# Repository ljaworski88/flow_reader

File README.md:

# Streaming Potential Calculator

This is a pyqt5 application intended to be used with the sensor board included in the src/kicad folder and the Raspberry Pi.

The application is intended to determine the streaming potential of tissues placed within a chamber designed by my collegue by interfacing with two NAU7802 24-bit ADCs connected to seperate pressure transducers, the Sensirion SLG-150 flow meter, and the Keithley 6514 Electrometer.
The included install script should install the application and all required dependancies on a fresh Raspberry Pi install (changing the way sudo operates by default on the pi will break this functionality).

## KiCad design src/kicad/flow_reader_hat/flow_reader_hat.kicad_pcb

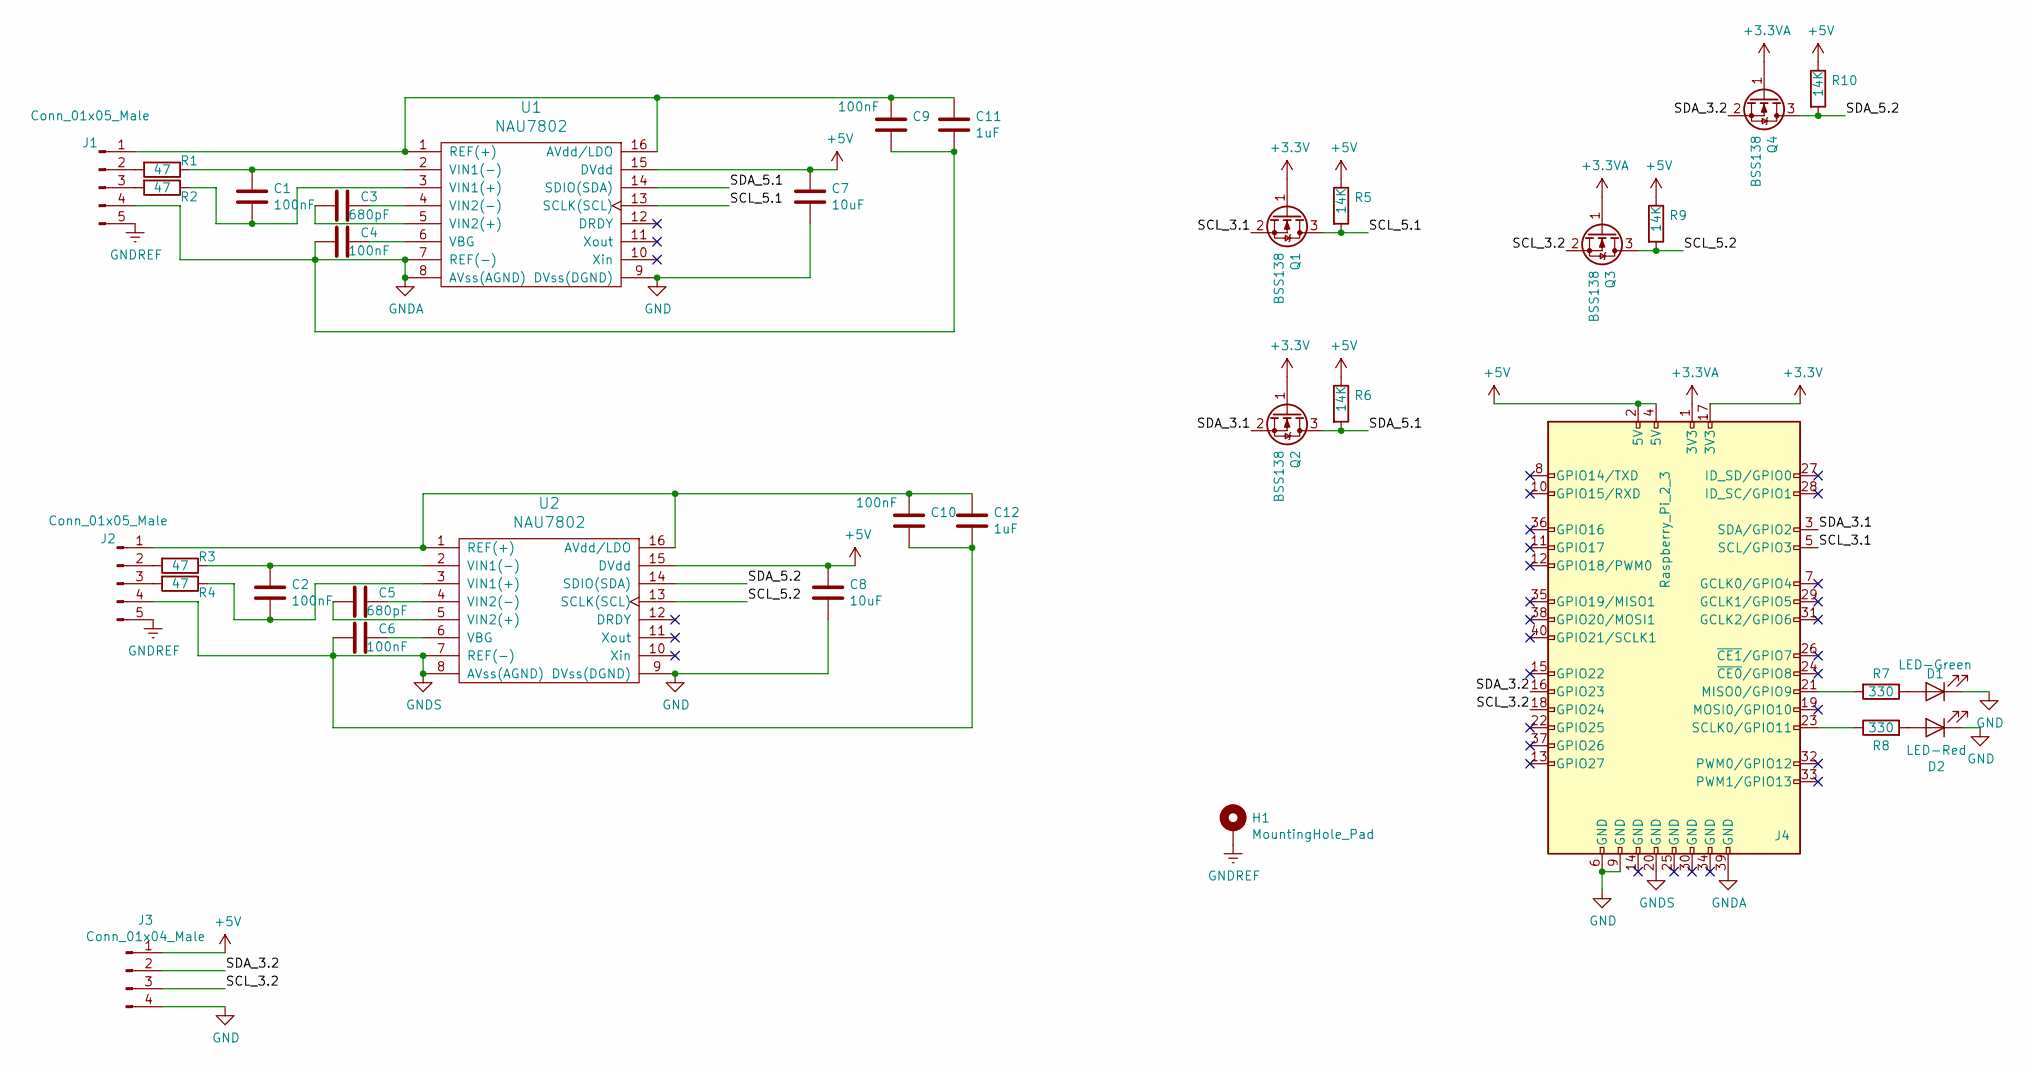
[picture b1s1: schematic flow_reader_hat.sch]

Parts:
C1, C2, C4, C6, C9, C10: 100nF; C_1206_3216Metric
C3, C5: 680pF; C_0805_2012Metric
C7, C8: 10uF; C_0805_2012Metric
C11, C12: 1uF; C_0805_2012Metric
D1: LED-Green; LED_0603_1608Metric_Castellated
D2: LED-Red; LED_0603_1608Metric_Castellated
H1: MountingHole_Pad; Banana_Jack_1Pin
J1, J2: Conn_01x05_Male; JST_EH_S5B-EH_1x05_P2.50mm_Horizontal
J3: Conn_01x04_Male; JST_EH_S4B-EH_1x04_P2.50mm_Horizontal
J4: Raspberry_Pi_2_3; Raspberry_Pi_Zero_Socketed_THT_FaceDown_MountingHoles
Q1, Q2, Q3, Q4: BSS138; SOT-23
R1, R2, R3, R4: 47; R_0805_2012Metric
R5, R6, R9, R10: 14K; R_0805_2012Metric
R7, R8: 330; R_0805_2012Metric
U1, U2: NAU7802; SOP-16_4.4x10.4mm_P1.27mm

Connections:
+3.3VA: J4.1 (3V3), Q3.1 (G), Q4.1 (G)
+3V3: J4.17 (3V3), Q1.1 (G), Q2.1 (G)
+5V: C7.1, C8.1, J3.1, J4.2 (5V), J4.4 (5V), R5.1, R6.1, R9.1, R10.1, U1.15 (DVdd), U2.15 (DVdd)
/SCL_3.1: J4.5 (SCL/GPIO3), Q1.2 (S)
/SCL_3.2: J3.3, J4.18 (GPIO24), Q3.2 (S)
/SCL_5.1: Q1.3 (D), R5.2, U1.13 (SCLK(SCL))
/SCL_5.2: Q3.3 (D), R9.2, U2.13 (SCLK(SCL))
/SDA_3.1: J4.3 (SDA/GPIO2), Q2.2 (S)
/SDA_3.2: J3.2, J4.16 (GPIO23), Q4.2 (S)
/SDA_5.1: Q2.3 (D), R6.2, U1.14 (SDIO(SDA))
/SDA_5.2: Q4.3 (D), R10.2, U2.14 (SDIO(SDA))
GND: C7.2, C8.2, D1.1 (K), D2.1 (K), J3.4, J4.6 (GND), J4.9 (GND), U1.9 (DVss(DGND)), U2.9 (DVss(DGND))
GNDA: C4.2, C9.2, C11.2, J1.4, J4.39 (GND), U1.7 (REF(-)), U1.8 (AVss(AGND))
GNDREF: H1.1, J1.5, J2.5
GNDS: C6.2, C10.2, C12.2, J2.4, J4.20 (GND), U2.7 (REF(-)), U2.8 (AVss(AGND))
unnamed: C1.1, R2.1, U1.3 (VIN1(+))
unnamed: C1.2, R1.1, U1.2 (VIN1(-))
unnamed: C2.1, R4.1, U2.3 (VIN1(+))
unnamed: C2.2, R3.1, U2.2 (VIN1(-))
unnamed: C3.1, U1.4 (VIN2(-))
unnamed: C3.2, U1.5 (VIN2(+))
unnamed: C4.1, U1.6 (VBG)
unnamed: C5.1, U2.4 (VIN2(-))
unnamed: C5.2, U2.5 (VIN2(+))
unnamed: C6.1, U2.6 (VBG)
unnamed: C10.1, C12.1, J2.1, U2.1 (REF(+)), U2.16 (AVdd/LDO)
unnamed: C9.1, C11.1, J1.1, U1.1 (REF(+)), U1.16 (AVdd/LDO)
unnamed: D1.2 (A), R7.1
unnamed: D2.2 (A), R8.2
unnamed: J1.2, R1.2
unnamed: J1.3, R2.2
unnamed: J2.2, R3.2
unnamed: J2.3, R4.2
unnamed: J4.21 (MISO0/GPIO9), R7.2
unnamed: J4.23 (SCLK0/GPIO11), R8.1

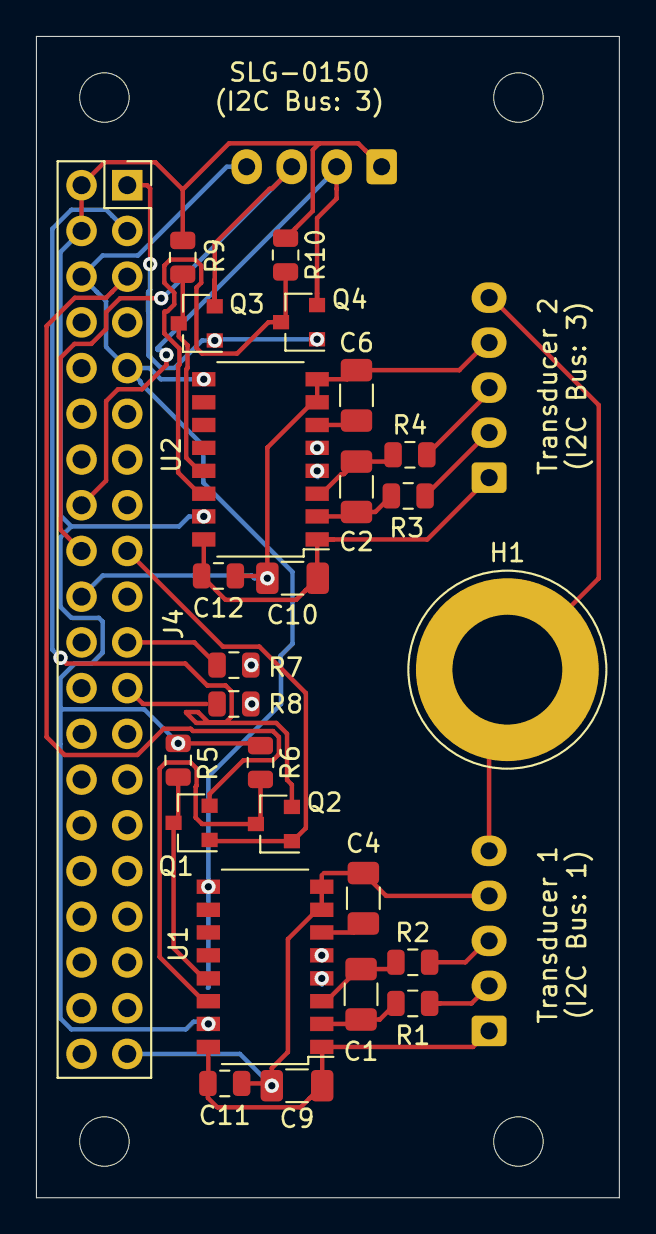
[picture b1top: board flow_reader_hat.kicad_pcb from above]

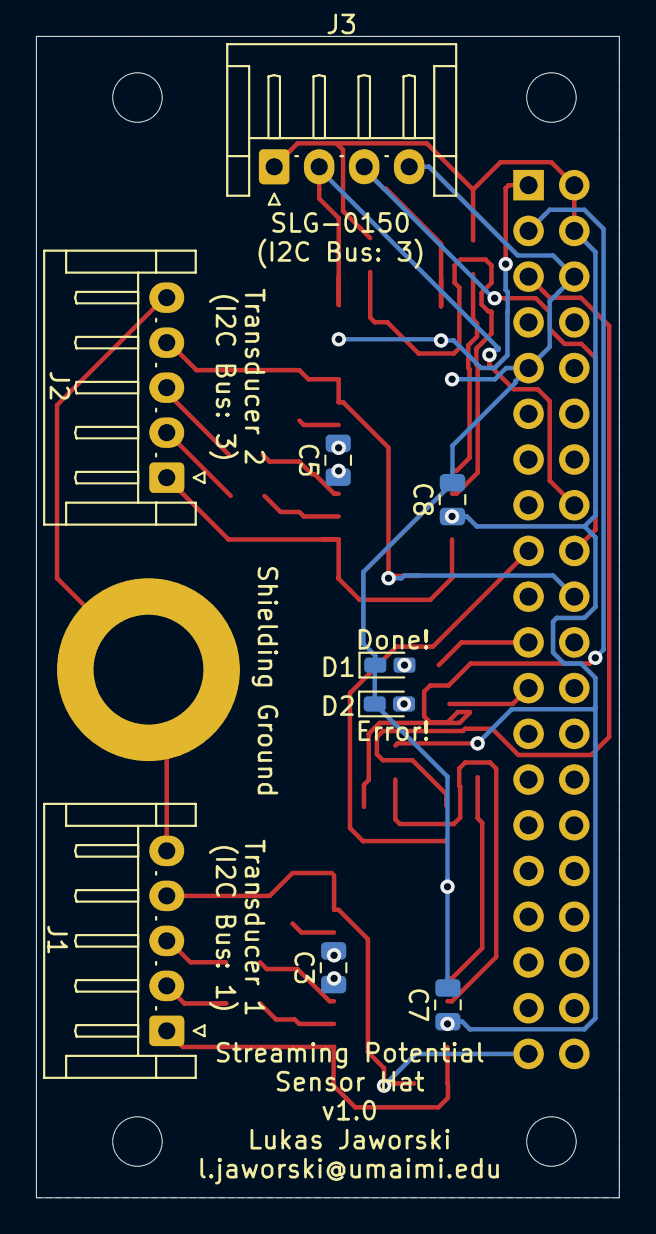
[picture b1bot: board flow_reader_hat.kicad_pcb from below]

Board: 2 copper layers, 32.4 x 64.5 mm, 35 parts (9 on the bottom side), 35 nets.

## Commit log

2020-07-29 Added License
2020-07-29 Added README
2020-07-29 fixed typo
2020-07-30 making the UI and generating the .ui file
2020-07-30 more UI work
2020-07-31 made a first quick and dirty version of the functional flow meter side, more to come
2020-07-31 changed a logic test that had some errors
2020-08-03 Added a UI and many functions
2020-08-03 removed the testui file as it no longer used
2020-08-03 small variable renaming
2020-08-03 fixed bug where hitting run again wouldn't activate lockout time
2020-08-03 minor bugfixes and getting rid of unneeded status messages
2020-08-03 Made the flow reader exectuable
2020-08-06 adding hardware design files and a done sound
2020-08-06 changed sf04 sensor library from local folder to python installed package
2020-08-06 changed sound playback function
2020-08-19 Designed sensor hat and fixed up global save code
2020-08-19 Fixed bad variable name
2020-08-20 Added memory to program settings
2020-08-20 minor bug fix
2020-08-21 Fixed the global settings mechanism, so now all settings are remembered as they are changed. Also added a logo, very important, from openclipart.com
2020-08-21 reactivated the smbus for testing on the pi
2020-08-27 Added in the reamining graphing functionality, prepped for the pressure readings, added a calibration tab and a few other small changes
2020-08-27 renamed the .ui file to MainWindow because it was messing with my bash autocomplete to open the main python code file
2020-08-28 added data logging of live data
2020-08-28 Changed the done notification sound
2020-08-28 fixed sound on done, added led function, adding unit change on graph function
2020-08-31 Did a bunch of UI and unit conversion work, also fixed changed to that only SI units are held in the back end
2020-08-31 checking to see if this fixes the flow rate graph range
2020-08-31 fixed unit conversion bug and pressure graph bug
2020-08-31 Chancge a qt combobox signal from indexChanged to activated to get rid of a bug where a function was called unnecessarily
2020-08-31 bug hunting
2020-08-31 more testing
2020-09-02 Adding all sensor options as the boards came in and I need to test them
2020-09-02 typo fix #bajillion
2020-09-02 added the self callback for a i2c call
2020-09-02 added .text() to some QlineEdit calls to get the text and not the object itself
2020-09-02 fixed the sourcemeter reading code
2020-09-03 Added more to the calibration feature, also fixed the set error bounds functions
2020-09-03 removed Keithely manual from tracking
2020-09-03 explictly set a float to string so that it can be placed in the QLineEdit
2020-09-03 Fixing the options at boot in the errorBoundsComboBox
2020-09-03 truncated the float in the errorbounds setpoint to an int
2020-09-03 More fixes to the flow error bounds code
2020-09-03 fixed up the calibration graph
2020-09-03 Renamed left and right transducers to transducers 2 and 1 respectively due to the hardware design and writing
2020-09-03 got rid of divide by zero error
2020-09-03 fixed global-settings names
2020-09-03 fixed some addressing issues and added LED status blinking and perma on
2020-09-08 added save calibration feature
2020-09-08 forgot to add the self call to a qt signal
2020-09-08 the zip file needs a byteslike object
2020-09-08 still fixing the last issue
2020-09-08 still fixing zipfile functionality
2020-09-08 please actually write the zip file this time
2020-09-08 fixing yaml formatting
2020-09-08 added load settings function
2020-09-08 bleh
2020-09-08 added load calibration file feature
2020-09-08 temporary chang to pressuredifferential because only one sensor is connected
2020-09-08 fixed input validator for calibration save file
2020-09-09 fixed electrometer code, added results calculation
2020-09-09 removed all current reading code as it is unneeded
2020-09-09 forgot a call to self
2020-09-09 fixing saving results function
2020-09-09 fix the results
2020-09-14 changed to read voltage only at end to not degrade electrodes, added install script, added GUI for conductivity measurement
2020-09-14 updated install script
2020-09-15 updated install script, added error checking for normal operation, and renamed some UI elements for future work
2020-09-15 fixed error message code
2020-09-15 Fixing error meassages
2020-09-15 fixing save settings functions
2020-09-15 changed install script to omit the gpio overlay bit as they may have fixed the offical image
2020-09-15 fixed install script and keithley electrometer detection
2020-09-15 finalized install script
2020-09-16 fixed pressure differential
